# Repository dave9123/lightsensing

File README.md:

# Lightsensing
A board that turns an LED on if no light is detected. Gerbers can be found at [pcb/gerber_to_order](./pcb/gerber_to_order)

## Features
1. Customizable photoresistor resistance using a potentiometer
2. Small design

## BOM
1. 1x Keystone 3034 CR2032 Battery Holder
2. 1x 3362P-1-103 Potentiometer
3. 1x 2N3906 PNP Transistor
4. 1x THT LED
5. 220 Ohm THT Resistor
6. 47k Ohm THT Resistor

| Schematics | PCB | 3D View |
| :-: | :-: | :-: |
|  |  |  |

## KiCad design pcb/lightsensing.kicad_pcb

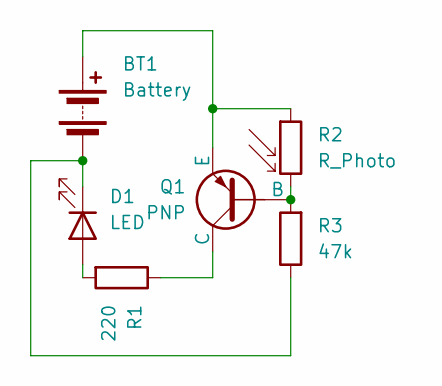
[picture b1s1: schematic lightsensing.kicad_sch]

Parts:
BT1: Battery; BatteryHolder_Keystone_3034_1x20mm
D1: LED; LED_D5.0mm_Clear
Q1: PNP; TO-92_Inline
R1: 220; R_Axial_DIN0207_L6.3mm_D2.5mm_P2.54mm_Vertical
R2: R_Photo; R_LDR_5.0x4.1mm_P3mm_Vertical
R3: 47k; R_Axial_DIN0207_L6.3mm_D2.5mm_P2.54mm_Vertical

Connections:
unnamed: BT1.1 (+), Q1.3 (E), R2.1
unnamed: BT1.2 (-), D1.1 (K), R3.1
unnamed: D1.2 (A), R1.2
unnamed: Q1.2 (B), R2.2, R3.2
unnamed: Q1.1 (C), R1.1

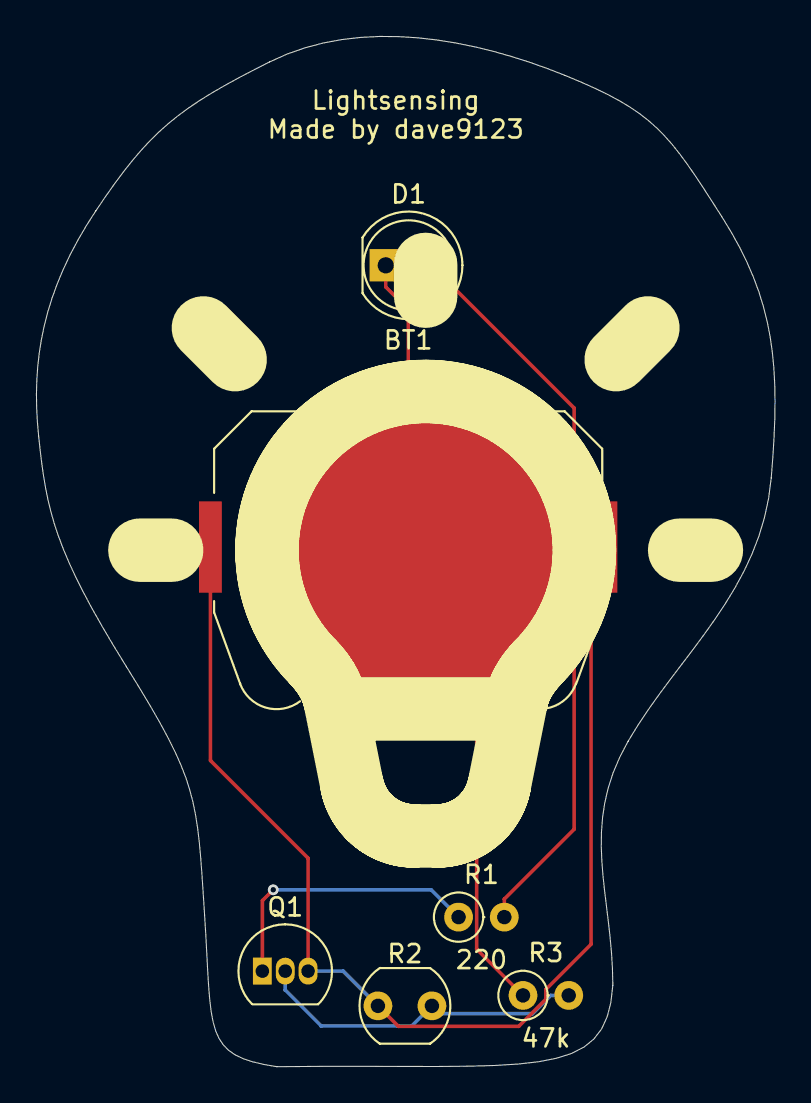
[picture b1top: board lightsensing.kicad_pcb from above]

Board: 2 copper layers, 41.0 x 57.2 mm, 6 parts (0 on the bottom side), 5 nets.

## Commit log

2025-04-27 Gerbers
2025-04-30 Added some silkscreen and weird looking design
2025-06-07 Updated silkscreen
